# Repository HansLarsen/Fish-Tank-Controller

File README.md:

# Fish-Tank-Controller
A fish tank controller hat, for the Arduino Mega.

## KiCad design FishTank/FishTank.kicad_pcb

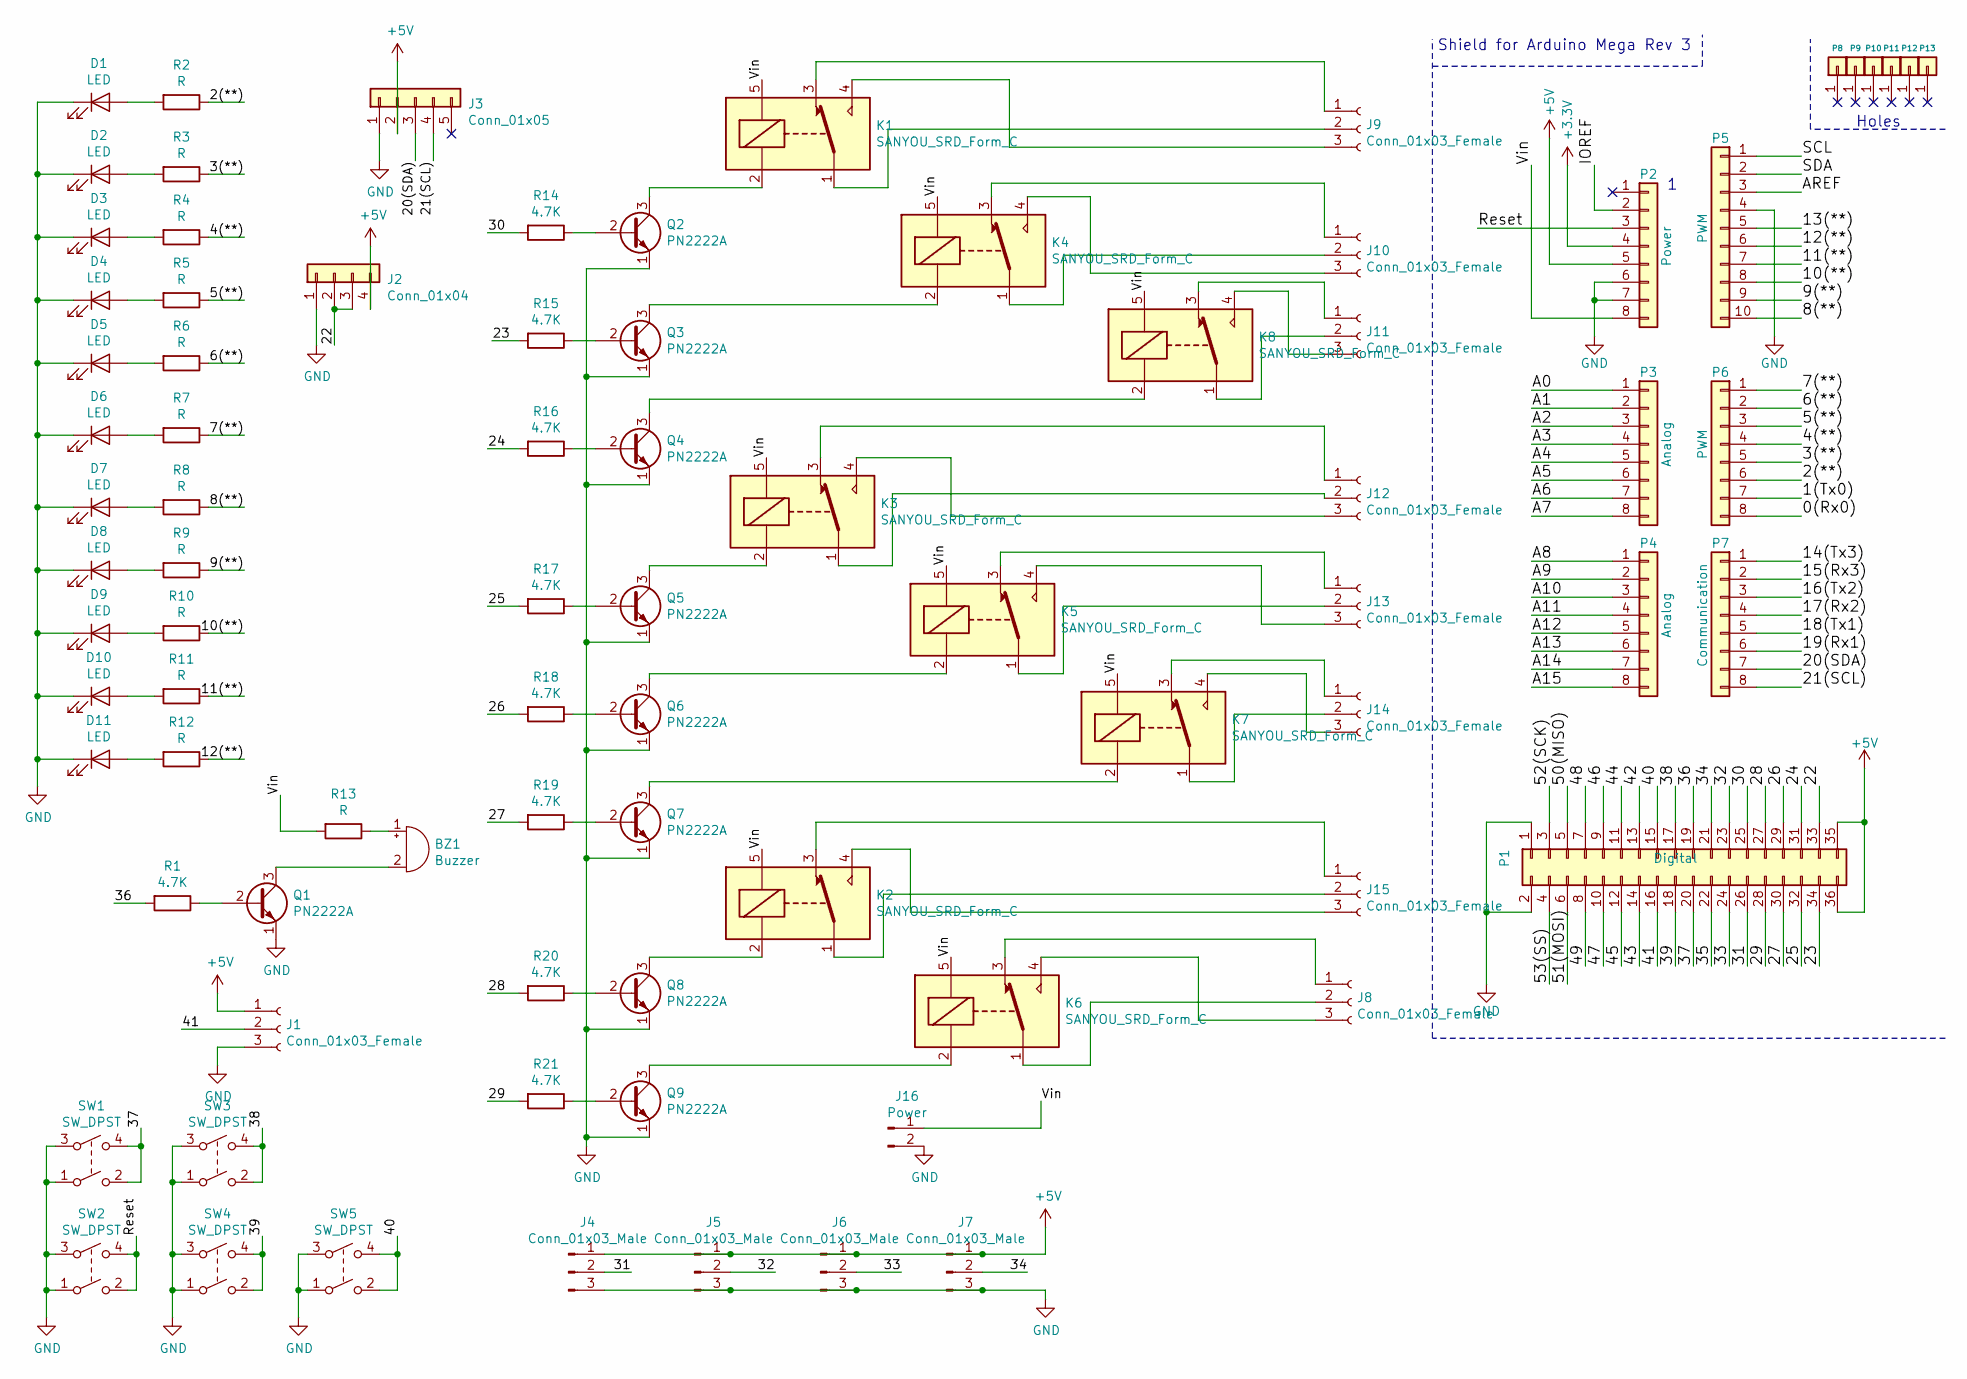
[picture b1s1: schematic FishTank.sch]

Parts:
BZ1: Buzzer; Buzzer_12x9.5RM7.6
D1, D2, D3, D4, D5, D6, D7, D8, D9, D10, D11: LED; LED_D5.0mm_Horizontal_O6.35mm_Z3.0mm
J1: Conn_01x03_Female; PinHeader_1x03_P2.54mm_Horizontal
J2: Conn_01x04; PinHeader_1x04_P2.54mm_Horizontal
J3: Conn_01x05; PinHeader_1x05_P2.54mm_Horizontal
J4, J5, J6, J7: Conn_01x03_Male; TerminalBlock_bornier-3_P5.08mm
J8, J9, J10, J11, J12, J13, J14, J15: Conn_01x03_Female; TerminalBlock_Altech_AK300-3_P5.00mm
J16: Power; TerminalBlock_Altech_AK300-2_P5.00mm
K1, K2, K3, K4, K5, K6, K7, K8: SANYOU_SRD_Form_C; Relay_SPDT_SANYOU_SRD_Series_Form_C
P1: Digital; Socket_Strip_Arduino_2x18
P2: Power; Socket_Strip_Arduino_1x08
P3, P4: Analog; Socket_Strip_Arduino_1x08
P5: PWM; Socket_Strip_Arduino_1x10
P6: PWM; Socket_Strip_Arduino_1x08
P7: Communication; Socket_Strip_Arduino_1x08
P8, P9, P10, P11, P12, P13: CONN_01X01; Arduino_1pin
Q1, Q2, Q3, Q4, Q5, Q6, Q7, Q8, Q9: PN2222A; TO-92_Inline
R1, R14, R15, R16, R17, R18, R19, R20, R21: 4.7K; R_Axial_DIN0204_L3.6mm_D1.6mm_P7.62mm_Horizontal
R2, R3, R4, R5, R6, R7, R8, R9, R10, R11, R12, R13: R; R_Axial_DIN0204_L3.6mm_D1.6mm_P7.62mm_Horizontal
SW1, SW2, SW3, SW4, SW5: SW_DPST; SW_PUSH_6mm_H5mm

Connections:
+3V3: P2.4
+5V: J1.1, J2.4, J3.2, J4.1, J5.1, J6.1, J7.1, P1.35, P1.36, P2.5
/0(Rx0): P6.8
/1(Tx0): P6.7
/2(**): P6.6, R2.1
/3(**): P6.5, R3.1
/4(**): P6.4, R4.1
/5(**): P6.3, R5.1
/6(**): P6.2, R6.1
/7(**): P6.1, R7.1
/8(**): P5.10, R8.1
/9(**): P5.9, R9.1
/10(**): P5.8, R10.1
/11(**): P5.7, R11.1
/12(**): P5.6, R12.1
/13(**): P5.5
/14(Tx3): P7.1
/15(Rx3): P7.2
/16(Tx2): P7.3
/17(Rx2): P7.4
/18(Tx1): P7.5
/19(Rx1): P7.6
/20(SDA): J3.3, P7.7
/21(SCL): J3.4, P7.8
/22: J2.2, J2.3, P1.33
/23: P1.34, R15.2
/24: P1.31, R16.2
/25: P1.32, R17.2
/26: P1.29, R18.2
/27: P1.30, R19.2
/28: P1.27, R20.2
/29: P1.28, R21.2
/30: P1.25, R14.2
/31: J4.2, P1.26
/32: J5.2, P1.23
/33: J6.2, P1.24
/34: J7.2, P1.21
/35: P1.22
/36: P1.19, R1.2
/37: P1.20, SW1.2, SW1.4
/38: P1.17, SW3.2, SW3.4
/39: P1.18, SW4.2, SW4.4
/40: P1.15, SW5.2, SW5.4
/41: J1.2, P1.16
/42: P1.13
/43: P1.14
/44: P1.11
/45: P1.12
/46: P1.9
/47: P1.10
/48: P1.7
/49: P1.8
/50(MISO): P1.5
/51(MOSI): P1.6
/52(SCK): P1.3
/53(SS): P1.4
/A0: P3.1
/A1: P3.2
/A2: P3.3
/A3: P3.4
/A4: P3.5
/A5: P3.6
/A6: P3.7
/A7: P3.8
/A8: P4.1
/A9: P4.2
/A10: P4.3
/A11: P4.4
/A12: P4.5
/A13: P4.6
/A14: P4.7
/A15: P4.8
/AREF: P5.3
/IOREF: P2.2
/Reset: P2.3, SW2.2, SW2.4
/SCL: P5.1
/SDA: P5.2
/Vin: J16.1, K1.5, K2.5, K3.5, K4.5, K5.5, K6.5, K7.5, K8.5, P2.8, R13.2
GND: D1.1 (K), D2.1 (K), D3.1 (K), D4.1 (K), D5.1 (K), D6.1 (K), D7.1 (K), D8.1 (K), D9.1 (K), D10.1 (K), D11.1 (K), J1.3, J2.1, J3.1, J4.3, J5.3, J6.3, J7.3, J16.2, P1.1, P1.2, P2.6, P2.7, P5.4, Q1.1 (E), Q2.1 (E), Q3.1 (E), Q4.1 (E), Q5.1 (E), Q6.1 (E), Q7.1 (E), Q8.1 (E), Q9.1 (E), SW1.1, SW1.3, SW2.1, SW2.3, SW3.1, SW3.3, SW4.1, SW4.3, SW5.1, SW5.3
unnamed: BZ1.1 (-), R13.1
unnamed: BZ1.2 (+), Q1.3 (C)
unnamed: D1.2 (A), R2.2
unnamed: D2.2 (A), R3.2
unnamed: D3.2 (A), R4.2
unnamed: D4.2 (A), R5.2
unnamed: D5.2 (A), R6.2
unnamed: D6.2 (A), R7.2
unnamed: D7.2 (A), R8.2
unnamed: D8.2 (A), R9.2
unnamed: D9.2 (A), R10.2
unnamed: D10.2 (A), R11.2
unnamed: D11.2 (A), R12.2
unnamed: J8.1, K6.3
unnamed: J8.2, K6.1
unnamed: J8.3, K6.4
unnamed: J9.1, K1.3
unnamed: J9.2, K1.1
unnamed: J9.3, K1.4
unnamed: J10.1, K4.3
unnamed: J10.2, K4.1
unnamed: J10.3, K4.4
unnamed: J11.1, K8.3
unnamed: J11.2, K8.1
unnamed: J11.3, K8.4
unnamed: J12.1, K3.3
unnamed: J12.2, K3.1
unnamed: J12.3, K3.4
unnamed: J13.1, K5.3
unnamed: J13.2, K5.1
unnamed: J13.3, K5.4
unnamed: J14.1, K7.3
unnamed: J14.2, K7.1
unnamed: J14.3, K7.4
unnamed: J15.1, K2.3
unnamed: J15.2, K2.1
unnamed: J15.3, K2.4
unnamed: K1.2, Q2.3 (C)
unnamed: K2.2, Q8.3 (C)
unnamed: K3.2, Q5.3 (C)
unnamed: K4.2, Q3.3 (C)
unnamed: K5.2, Q6.3 (C)
unnamed: K6.2, Q9.3 (C)
unnamed: K7.2, Q7.3 (C)
unnamed: K8.2, Q4.3 (C)
unnamed: Q1.2 (B), R1.1
unnamed: Q2.2 (B), R14.1
unnamed: Q3.2 (B), R15.1
unnamed: Q4.2 (B), R16.1
unnamed: Q5.2 (B), R17.1
unnamed: Q6.2 (B), R18.1
unnamed: Q7.2 (B), R19.1
unnamed: Q8.2 (B), R20.1
unnamed: Q9.2 (B), R21.1

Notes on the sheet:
Shield for Arduino Mega Rev 3
Holes

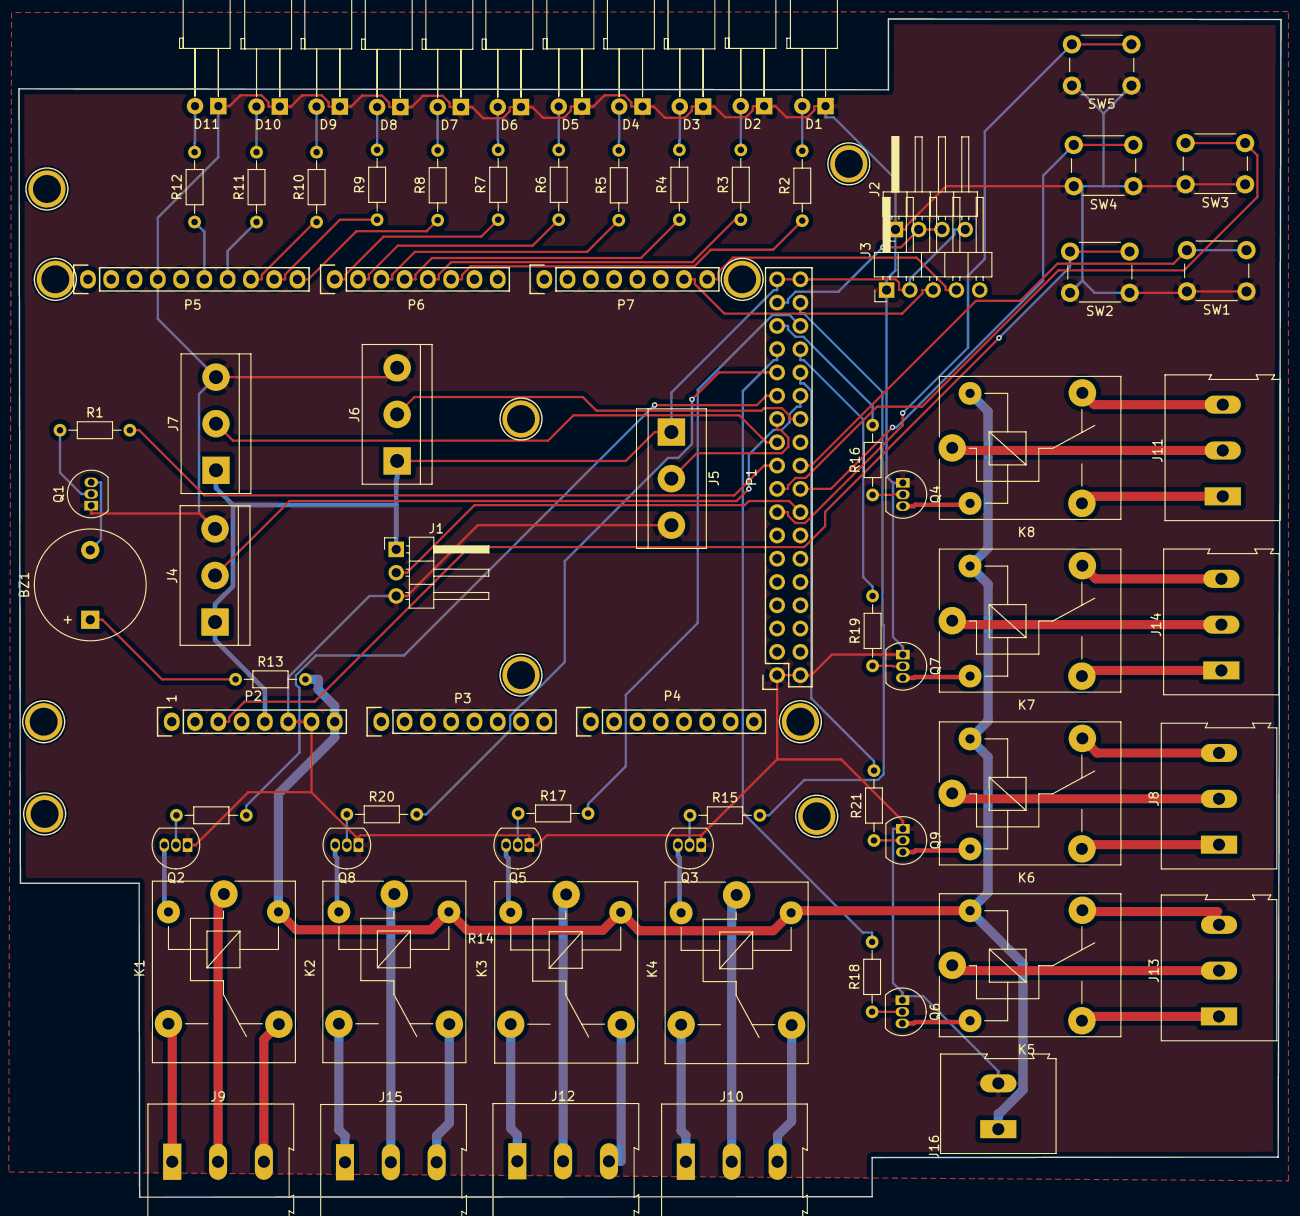
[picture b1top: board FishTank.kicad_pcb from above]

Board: 2 copper layers, 137.7 x 128.5 mm, 88 parts (0 on the bottom side), 90 nets.

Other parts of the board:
P14, P15, P16, P17: CONN_01X01; Arduino_1pin

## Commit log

2019-05-26 Initial Upload
2019-05-29 RefillProgramAdded
2019-05-29 Removed VSCODE file
2019-05-29 Fixed the refillprogram, so that it actually works
2019-05-30 Date Scheduler Finished, RTC working.
2019-06-01 Created an IOManager, rebuild refillprogram.
2019-06-01 Added Light Manager.
2019-06-01 Airpump Manager Added.
2019-06-02 Bug fix, prototype completion.
2019-06-02 Bug fixes.
2019-06-06 CO2 Manager added.
2019-06-06 Manager to control heater and filter.
2019-06-06 Buzzer added to heater program.
2019-06-06 Comment.
2019-06-06 Pin Change
